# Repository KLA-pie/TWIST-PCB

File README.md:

# TWIST-Lab
Olin College's Bio-Mimetic Soft Robotics lab (TWIST)

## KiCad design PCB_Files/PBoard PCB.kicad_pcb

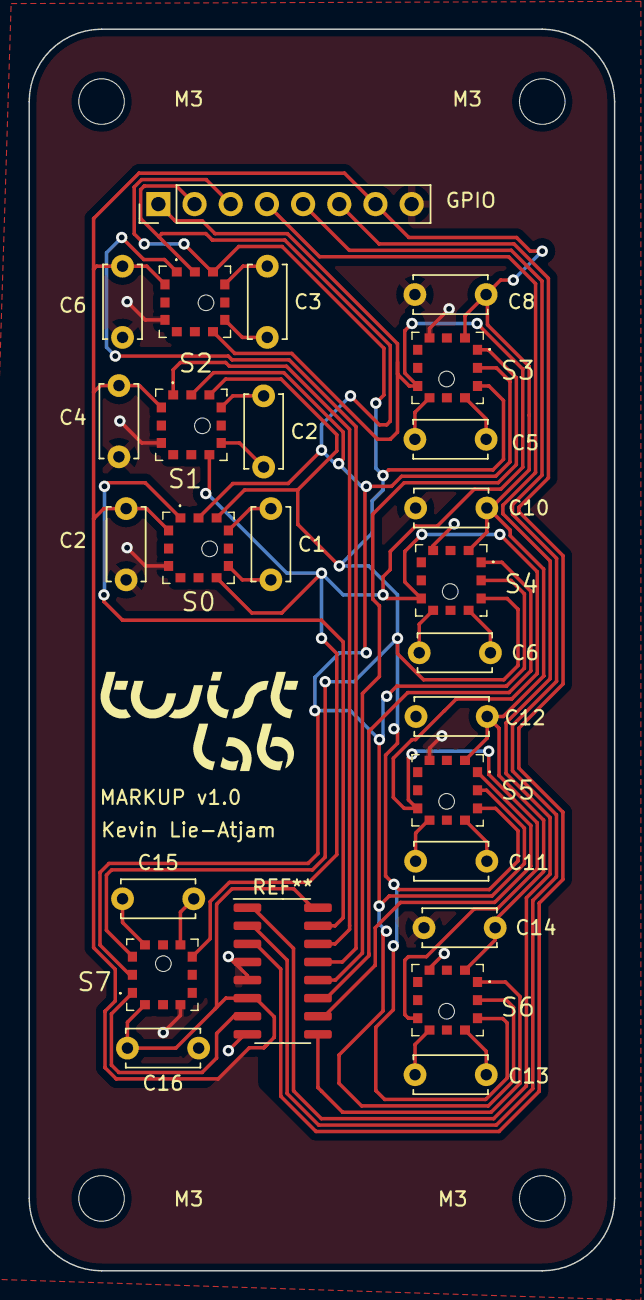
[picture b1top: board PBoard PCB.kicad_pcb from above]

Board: 2 copper layers, 41.1 x 87.2 mm, 32 parts (0 on the bottom side), 21 nets.

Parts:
C1, C2#2, C3, C5, C6, C11, C13, C15: 1 nF; C_Disc_D5.0mm_W2.5mm_P5.00mm
C2, C4, C6#2, C8, C10, C12, C14, C16: 0.1 μF; C_Disc_D5.0mm_W2.5mm_P5.00mm
Courtesy of: MountingHole_1.1mm
GPIO: Conn_01x08_Male; PinHeader_1x08_P2.54mm_Vertical
Kevin Lie-Atjam: MountingHole_1.1mm
M3, M3#2, M3#3, M3#4: MountingHole_3.2mm_M3
MARKUP v1.0: MountingHole_1.1mm
S0, S1, S2, S3, S4, S5, S6, S7: MPRLS02; MPRLS025BG0000SA

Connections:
+3V3: C2.1, C4.1, C6#2.1, C8.1, C10.1, C12.1, C14.1, C16.1, GPIO.7, S0.12 (VDD), S1.12 (VDD), S2.12 (VDD), S3.12 (VDD), S4.12 (VDD), S5.12 (VDD), S6.12 (VDD), S7.12 (VDD)
/CLK: GPIO.3, S0.3 (SCLK/SCL), S1.3 (SCLK/SCL), S2.3 (SCLK/SCL), S3.3 (SCLK/SCL), S4.3 (SCLK/SCL), S5.3 (SCLK/SCL), S6.3 (SCLK/SCL), S7.3 (SCLK/SCL)
/MISO: GPIO.1, S0.7 (MISO), S1.7 (MISO), S2.7 (MISO), S3.7 (MISO), S4.7 (MISO), S5.7 (MISO), S6.7 (MISO), S7.7 (MISO)
/MOSI: GPIO.2, S0.2 (MOSI/SDA), S1.2 (MOSI/SDA), S2.2 (MOSI/SDA), S3.2 (MOSI/SDA), S4.2 (MOSI/SDA), S5.2 (MOSI/SDA), S6.2 (MOSI/SDA), S7.2 (MOSI/SDA)
GND: C2.2, C4.2, C6#2.2, C8.2, C10.2, C12.2, C14.2, C16.2, GPIO.8, S0.10 (VSS), S1.10 (VSS), S2.10 (VSS), S3.10 (VSS), S4.10 (VSS), S5.10 (VSS), S6.10 (VSS), S7.10 (VSS)
unnamed: C2#2.1, S1.4 (VO+)
unnamed: C2#2.2, S1.6 (VO-)
unnamed: C3.1, S2.4 (VO+)
unnamed: C3.2, S2.6 (VO-)
unnamed: C5.1, S3.4 (VO+)
unnamed: C5.2, S3.6 (VO-)
unnamed: C6.1, S4.4 (VO+)
unnamed: C6.2, S4.6 (VO-)
unnamed: C11.1, S5.4 (VO+)
unnamed: C11.2, S5.6 (VO-)
unnamed: C13.1, S6.4 (VO+)
unnamed: C13.2, S6.6 (VO-)
unnamed: C15.1, S7.4 (VO+)
unnamed: C15.2, S7.6 (VO-)
unnamed: C1.1, S0.4 (VO+)
unnamed: C1.2, S0.6 (VO-)

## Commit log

2023-05-23 Moved files from olincollege/TWIST-Lab to personal repo
